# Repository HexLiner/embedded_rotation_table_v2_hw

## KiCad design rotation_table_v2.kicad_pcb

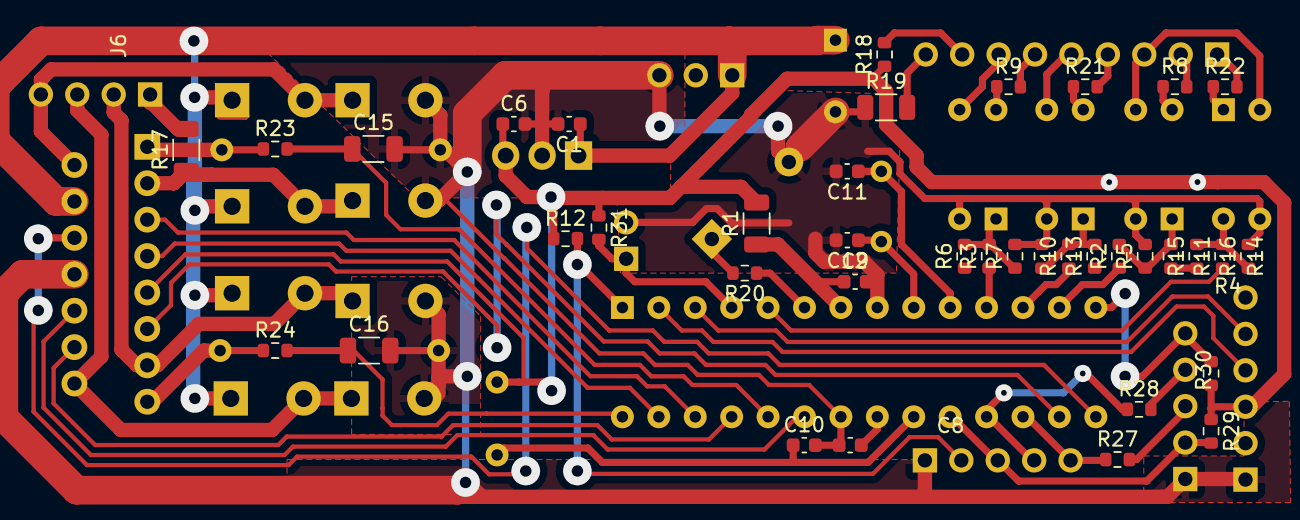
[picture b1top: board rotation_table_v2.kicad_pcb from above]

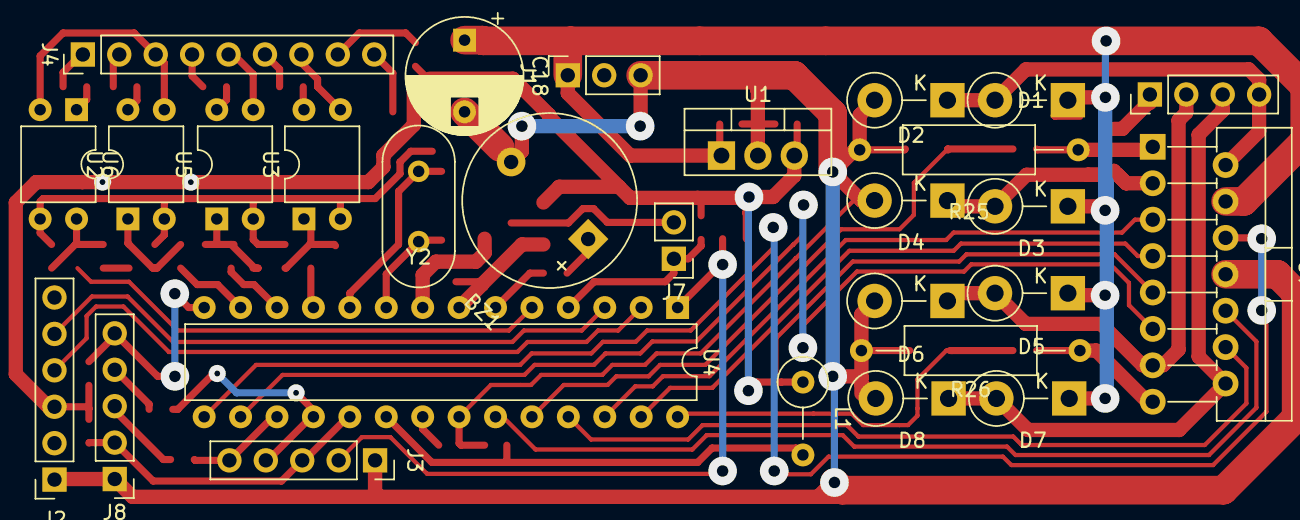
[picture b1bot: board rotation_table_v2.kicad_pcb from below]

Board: 2 copper layers, 66 parts (28 on the bottom side), 55 nets.

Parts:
BZ1: Buzzer; Buzzer_12x9.5RM7.6
C1: 330n; C_0603_1608Metric
C6, C8, C9, C10: 100n; C_0603_1608Metric
C11, C12: 22p; C_0603_1608Metric
C15, C16: 100n; C_1206_3216Metric
C18: 470u; CP_Radial_D8.0mm_P5.00mm
D1, D2, D3, D4, D5, D6, D7, D8: D; D_DO-15_P5.08mm_Vertical_KathodeUp
J1: POWER_CONN; PinSocket_1x03_P2.54mm_Vertical
J2: FTDI_COMM; PinSocket_1x06_P2.54mm_Vertical
J3: ISP; PinSocket_1x05_P2.54mm_Vertical
J4: EXT_CONN; PinHeader_1x09_P2.54mm_Vertical
J6: MT_CONN; PinHeader_1x04_P2.54mm_Vertical
J7: TAMPER_CONN; PinHeader_1x02_P2.54mm_Vertical
J8: HMI_CONN; PinHeader_1x05_P2.54mm_Vertical
L1: 10uH; L_Axial_L7.0mm_D3.3mm_P5.08mm_Vertical_Fastron_MICC
R1, R17: 0; R_1206_3216Metric
R2, R3, R10: 2k; R_0603_1608Metric
R4, R5, R6, R7, R8, R9, R11, R13, R14, R15, R16, R18, R21, R22, R27, R28: R; R_0603_1608Metric
R12, R29, R30, R31: 10k; R_0603_1608Metric
R19: R; R_1206_3216Metric
R20: 0; R_0603_1608Metric
R23, R24: 470; R_0603_1608Metric
R25, R26: 0.5; R_Axial_DIN0309_L9.0mm_D3.2mm_P15.24mm_Horizontal
U1: L7805; TO-220-3_Vertical
U2, U3, U5, U6: SFH617A-1; DIP-4_W7.62mm
U4: ATmega328-P; DIP-28_W7.62mm
U7: L298N; TO-220-15_P2.54x2.54mm_StaggerOdd_Lead4.58mm_Vertical
Y2: 8MHz; Crystal_HC18-U_Vertical

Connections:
+5V: C6.1, C9.1, J2.3, L1.1, R1.1, R1.2, R4.1, R6.1, R12.1, R13.1, R15.1, R18.1, R29.1, R30.1, R31.1, U1.3 (OUT), U4.7 (VCC), U7.9 (Vss)
+12V: C1.1, C18.1, D1.1 (K), D3.1 (K), D5.1 (K), D7.1 (K), J1.1, U1.1 (IN), U7.4 (Vs)
/BUZZER: R20.1, U4.6 (PD4)
/EXT_GND1: J4.3, U2.3, U6.2
/EXT_GND2: J4.5, U5.3
/EXT_GND3: J4.7, U3.3
/EXT_IN: R11.1, U4.5 (PD3)
/EXT_IN_ISO: J4.1, R22.2
/EXT_OUT1: R2.1, U4.13 (PD7)
/EXT_OUT1_ISO: J4.2, R8.2
/EXT_OUT2: R10.1, U4.12 (PD6)
/EXT_OUT2_ISO: J4.4, R21.2
/EXT_OUT3: R3.1, U4.11 (PD5)
/EXT_OUT3_ISO: J4.6, R9.2
/HOME_TAMPER: J7.1, R31.2, U4.4 (PD2)
/ISP_MISO_IND_STATUS: J3.4, R28.1, U4.18 (PB4)
/ISP_MOSI_IND_PROCESS: J3.5, R27.1, U4.17 (PB3)
/ISP_SCK_STOP_BUTTON: J3.3, J8.2, R29.2, U4.19 (PB5)
/MT_ENA_PWM: U4.15 (PB1), U7.6 (EnA)
/MT_ENB_PWM: U4.16 (PB2), U7.11 (EnB)
/MT_IN_1A: U4.26 (PC3), U7.5 (IN1)
/MT_IN_1A_EXT: D1.2 (A), D2.1 (K), J6.4, U7.2 (OUT1)
/MT_IN_1B: U4.23 (PC0), U7.10 (IN3)
/MT_IN_1B_EXT: D5.2 (A), D6.1 (K), J6.2, U7.13 (OUT3)
/MT_IN_2A: U4.27 (PC4), U7.7 (IN2)
/MT_IN_2A_EXT: D3.2 (A), D4.1 (K), R17.1, U7.3 (OUT2)
/MT_IN_2B: U4.25 (PC2), U7.12 (IN4)
/MT_IN_2B_EXT: D7.2 (A), D8.1 (K), J6.3, U7.14 (OUT4)
/RESET: J3.2, R12.2, U4.1 (~RESET/PC6)
/SENSA_ADC: C15.1, R23.2, U4.24 (PC1)
/SENSB_ADC: C16.1, R24.2, U4.28 (PC5)
/START_BUTTON: J8.5, R30.2, U4.14 (PB0)
/UART_RX: J2.4, U4.2 (PD0)
/UART_TX: J2.5, U4.3 (PD1)
GNDA: BZ1.2 (+), C1.2, C6.2, C8.2, C9.2, C10.2, C11.2, C12.2, C15.2, C16.2, C18.2, D2.2 (A), D4.2 (A), D6.2 (A), D8.2 (A), J1.3, J2.1, J3.1, J7.2, J8.1, R5.2, R7.2, R14.2, R16.2, R19.1, R25.2, R26.2, U1.2 (GND), U2.2, U3.2, U4.8 (GND), U4.22 (GND), U5.2, U6.3, U7.8 (GND)
unnamed: BZ1.1 (-), R20.2
unnamed: C8.1, U4.21 (AREF)
unnamed: C10.1, L1.2, U4.20 (AVCC)
unnamed: C11.1, U4.10 (XTAL2/PB7), Y2.1
unnamed: C12.1, U4.9 (XTAL1/PB6), Y2.2
unnamed: J4.8, R18.2
unnamed: J4.9, R19.2
unnamed: J6.1, R17.2
unnamed: J8.3, R27.2
unnamed: J8.4, R28.2
unnamed: R2.2, R4.2, R5.1, U2.1
unnamed: R3.2, R6.2, R7.1, U3.1
unnamed: R8.1, U2.4
unnamed: R9.1, U3.4
unnamed: R10.2, R13.2, R14.1, U5.1
unnamed: R11.2, R15.2, R16.1, U6.4
unnamed: R21.1, U5.4
unnamed: R22.1, U6.1
unnamed: R23.1, R25.1, U7.1 (SENSE_A)
unnamed: R24.1, R26.1, U7.15 (SENSE_B)

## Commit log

2025-09-18 Initial
